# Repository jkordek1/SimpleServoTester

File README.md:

# SimpleServoTester

##
Still WIP

## About
Simple project for quick on-the-go servo testing. It has two different modes, manual one for controlling the servo position via rotary encoder and automatic (sweep) mode.
 
## Project status
- [x] Breadboard prototype
- [x] Schematic
- [x] PCB
- [ ] Enclosure design
- [ ] 3D CAD assembly and renders
- [ ] Assembly
- [ ] Programming

## Main features
- Based on popular ATmega328p microcontroller used on Arduino boards
- Powered by 2x18650 batteries
- IN219 current sense IC
- Rotary encoder for mode selection

## BOM
The components used are the ones that were available at-hand during the process of development. Therefore BOM for this project is not optimal.

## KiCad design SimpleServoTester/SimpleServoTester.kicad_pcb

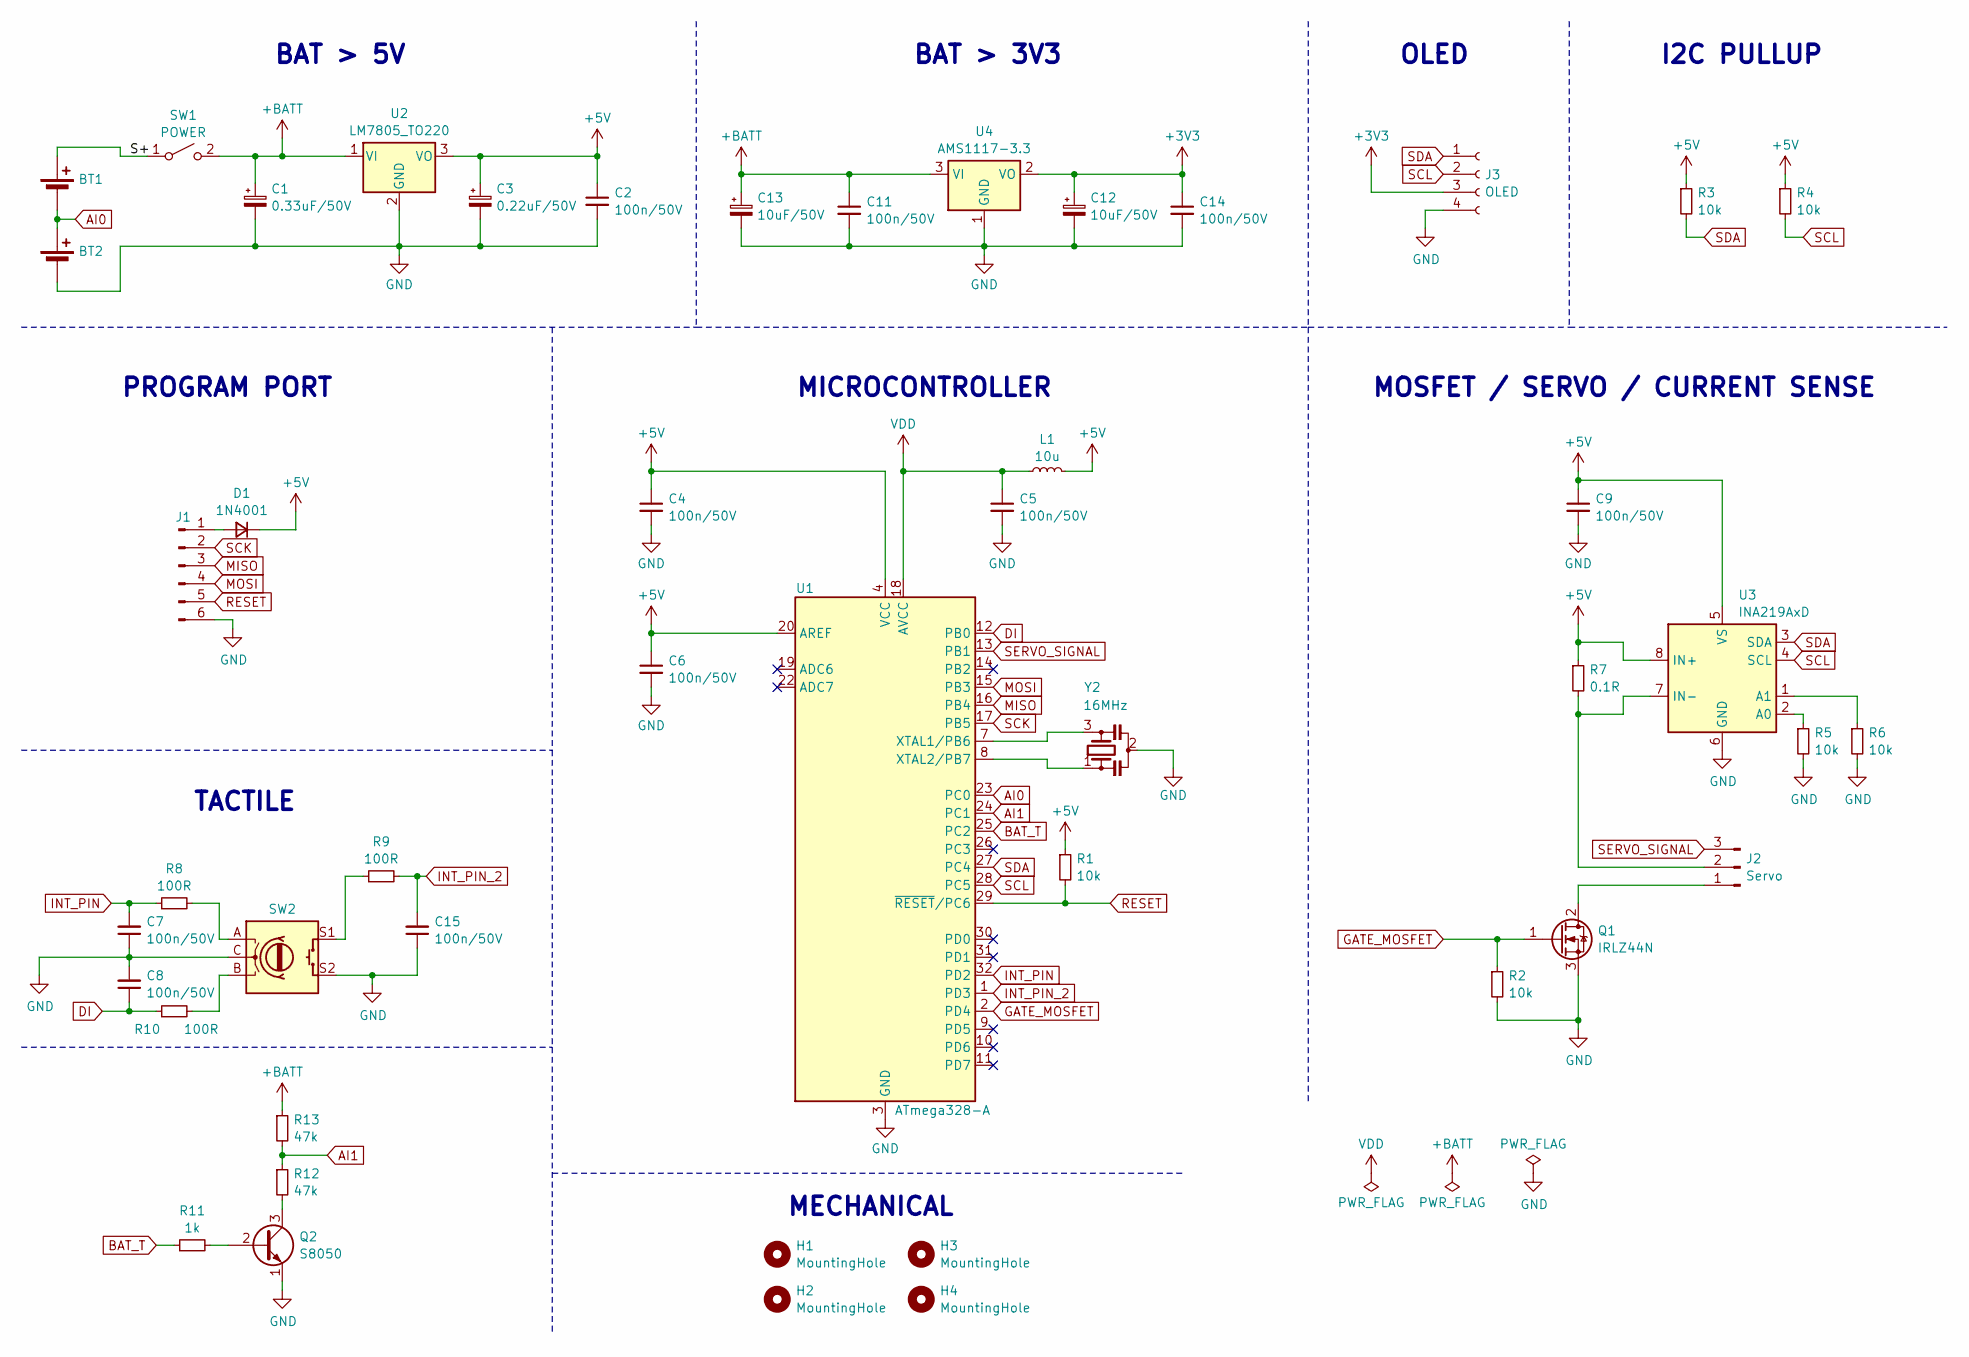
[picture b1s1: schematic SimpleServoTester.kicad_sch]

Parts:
BT1, BT2: Battery_Cell; 18650-PC2
C1: 0.33uF/50V; CP_Elec_5x5.4
C2, C4, C5, C6, C7, C8, C9, C11, C14, C15: 100n/50V; C_0603_1608Metric
C3: 0.22uF/50V; CP_Elec_5x5.4
C12, C13: 10uF/50V; CP_Elec_5x5.4
D1: 1N4001; D_SMA
H1, H2, H3, H4: MountingHole; MountingHole_3.2mm_M3
J1: USBASP; PinHeader_1x06_P2.54mm_Horizontal
J2: Servo; PinHeader_1x03_P2.54mm_Horizontal
J3: OLED; PinHeader_1x04_P2.54mm_Vertical
L1: 10u; L_1206_3216Metric
Q1: IRLZ44N; TO-220-3_Horizontal_TabDown
Q2: S8050; SOT-23-3
R1, R2, R3, R4, R5, R6: 10k; R_0603_1608Metric
R7: 0.1R; R_2512_6332Metric
R8, R9, R10: 100R; R_0603_1608Metric
R11: 1k; R_0603_1608Metric
R12, R13: 47k; R_0603_1608Metric
SW1: POWER; PinHeader_1x02_P2.54mm_Vertical
SW2: RotaryEncoder_Switch; RotaryEncoder_Alps_EC11E-Switch_Vertical_H20mm
U1: ATmega328-A; TQFP-32_7x7mm_P0.8mm
U2: LM7805_TO220; TO-220-3_Horizontal_TabDown
U3: INA219AxD; SOT-23-8
U4: AMS1117-3.3; SOT-223-3_TabPin2
Y2: 16MHz; CSTCE16M0V53-R0; JLCPCB Part # C32180

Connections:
+3V3: C12.1, C14.1, J3.3, U4.2 (VO)
+5V: C2.1, C3.1, C4.1, C6.1, C9.1, D1.1 (K), L1.2, R1.1, R3.1, R4.1, R7.1, U1.4 (VCC), U1.6 (VCC), U1.20 (AREF), U2.3 (VO), U3.5 (VS), U3.8 (IN+)
+BATT: C1.1, C11.1, C13.1, R13.1, SW1.2 (B), U2.1 (VI), U4.3 (VI)
/S+: BT1.1 (+), SW1.1 (A)
AI0: BT1.2 (-), BT2.1 (+), U1.23 (PC0)
AI1: R12.1, R13.2, U1.24 (PC1)
BAT_T: R11.1, U1.25 (PC2)
DI: C8.1, R10.1, U1.12 (PB0)
GATE_MOSFET: Q1.1 (G), R2.1, U1.2 (PD4)
GND: BT2.2 (-), C1.2, C2.2, C3.2, C4.2, C5.2, C6.2, C7.1, C8.2, C9.2, C11.2, C12.2, C13.2, C14.2, C15.1, J1.6, J3.4, Q1.3 (S), Q2.1 (E), R2.2, R5.2, R6.2, SW2.C, SW2.S2, U1.3 (GND), U1.5 (GND), U1.21 (GND), U2.2 (GND), U3.6 (GND), U4.1 (GND), Y2.2
INT_PIN: C7.2, R8.1, U1.32 (PD2)
INT_PIN_2: C15.2, R9.2, U1.1 (PD3)
MISO: J1.3, U1.16 (PB4)
MOSI: J1.4, U1.15 (PB3)
unnamed: D1.2 (A), J1.1
unnamed: J2.1, Q1.2 (D)
unnamed: J2.2, R7.2, U3.7 (IN-)
unnamed: Q2.2 (B), R11.2
unnamed: Q2.3 (C), R12.2
unnamed: R8.2, SW2.A
unnamed: R9.1, SW2.S1
unnamed: R10.2, SW2.B
unnamed: U1.7 (XTAL1/PB6), Y2.3
unnamed: U1.8 (XTAL2/PB7), Y2.1
unnamed: R5.1, U3.2 (A0)
unnamed: R6.1, U3.1 (A1)
RESET: J1.5, R1.2, U1.29 (~RESET/PC6)
SCK: J1.2, U1.17 (PB5)
SCL: J3.2, R4.2, U1.28 (PC5), U3.4 (SCL)
SDA: J3.1, R3.2, U1.27 (PC4), U3.3 (SDA)
SERVO_SIGNAL: J2.3, U1.13 (PB1)
VDD: C5.1, L1.1, U1.18 (AVCC)

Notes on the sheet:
OLED
TACTILE
BAT > 5V
I2C PULLUP
BAT > 3V3
MECHANICAL
MICROCONTROLLER
MOSFET / SERVO / CURRENT SENSE
PROGRAM PORT

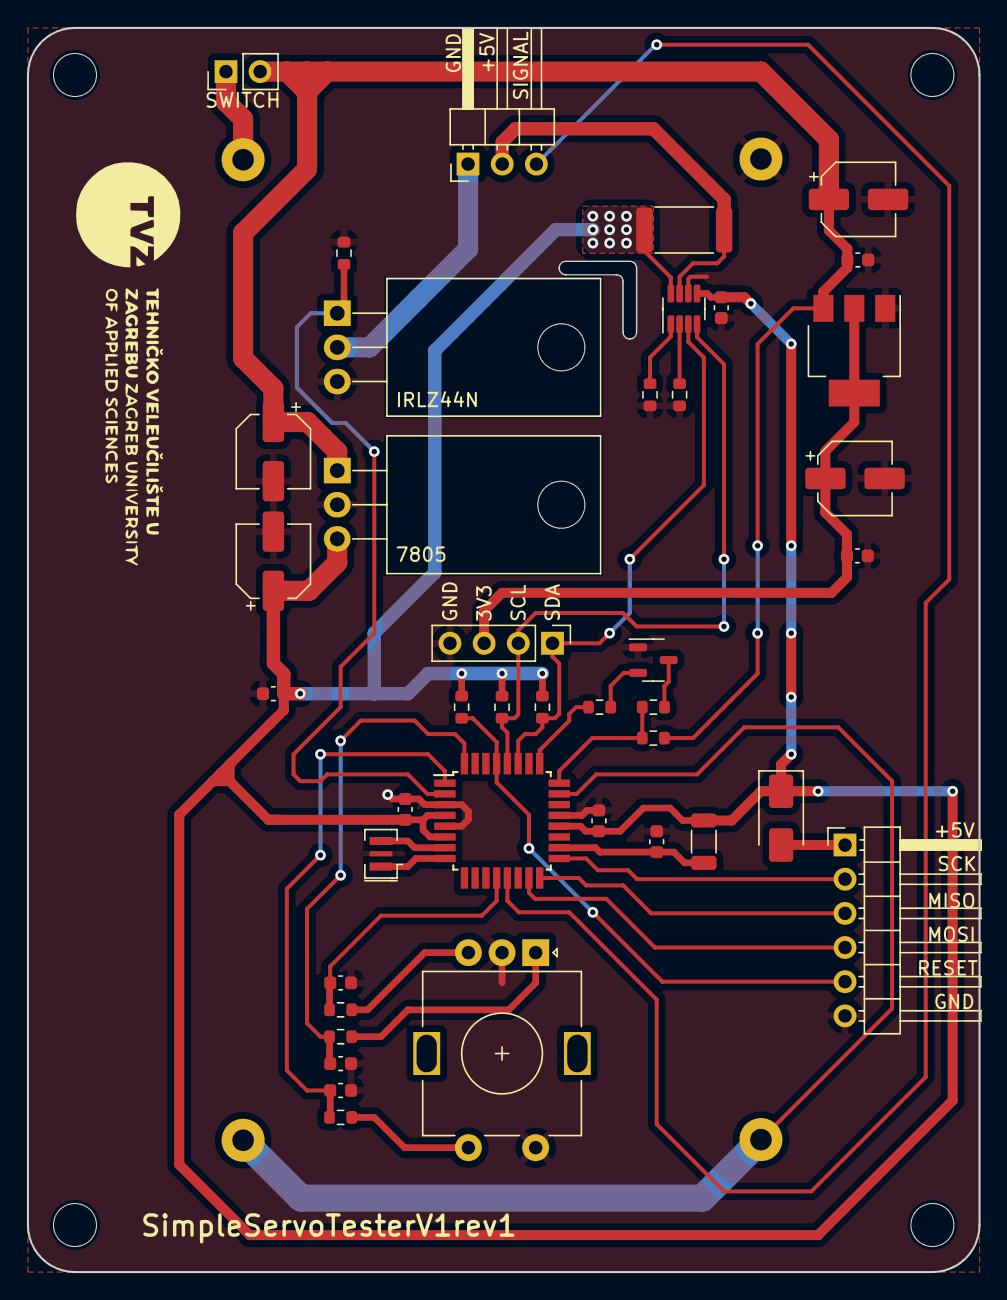
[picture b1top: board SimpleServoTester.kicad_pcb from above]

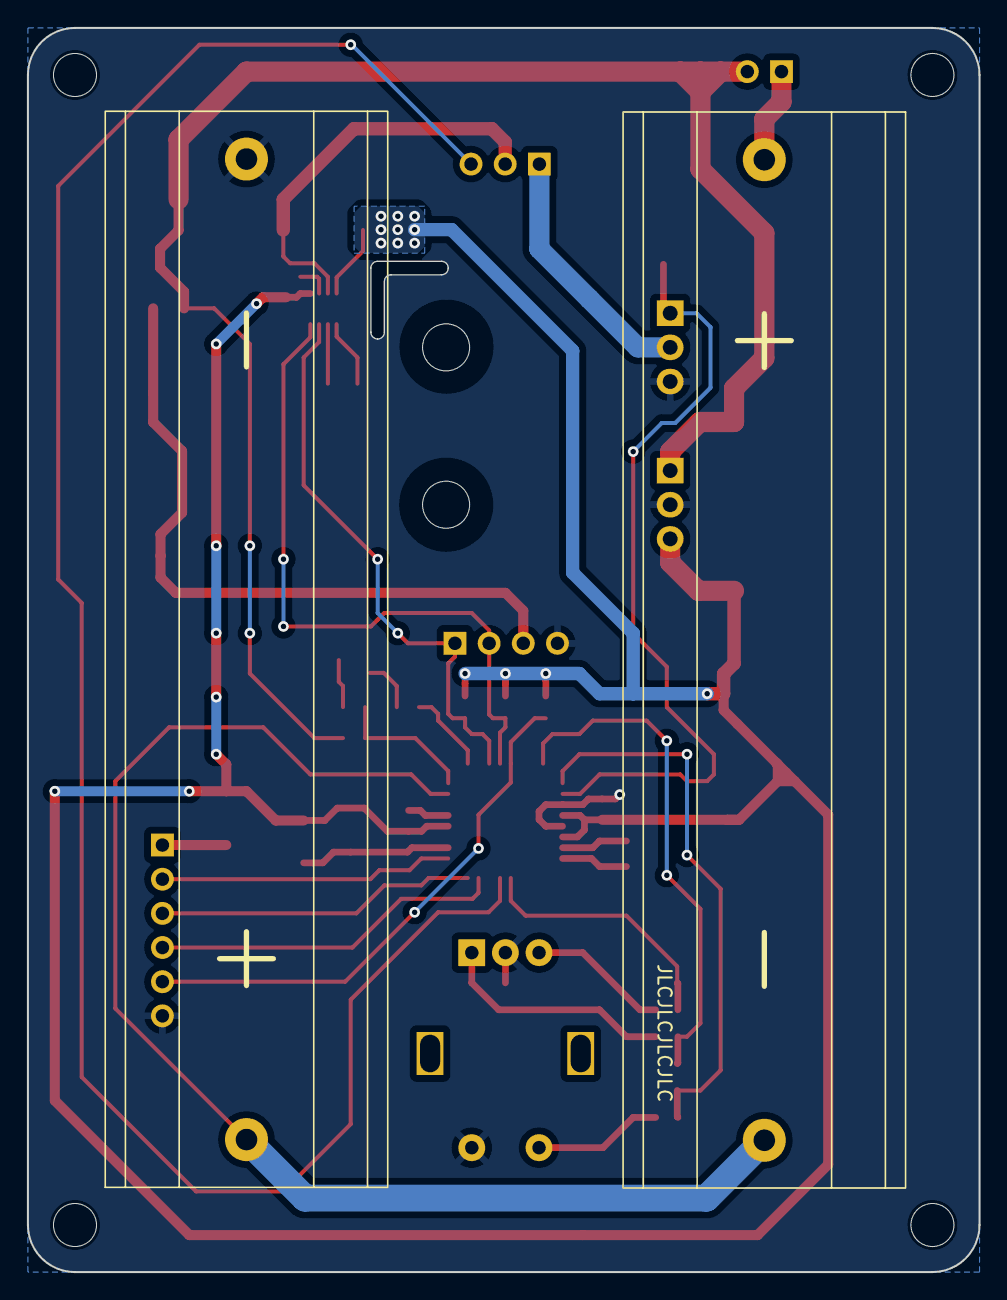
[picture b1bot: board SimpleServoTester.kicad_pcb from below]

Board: 2 copper layers, 70.8 x 92.5 mm, 47 parts (2 on the bottom side), 32 nets.

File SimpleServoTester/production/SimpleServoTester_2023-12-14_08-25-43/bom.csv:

Designator,Footprint,Quantity,Value,LCSC Part #
"BT1, BT2",18650-PC2,2,Battery_Cell,
C1,CP_Elec_5x5.4,1,0.33uF/50V,
"C11, C14, C15, C2, C4, C5, C6, C7, C8, C9",0603,10,100n/50V,
"C12, C13",CP_Elec_5x5.4,2,10uF/50V,
C3,CP_Elec_5x5.4,1,0.22uF/50V,
D1,D_SMA,1,1N4001,
"H1, H2, H3, H4",MountingHole_3.2mm_M3,4,MountingHole,
J1,PinHeader_1x06_P2.54mm_Horizontal,1,USBASP,
J2,PinHeader_1x03_P2.54mm_Horizontal,1,Servo,
J3,PinHeader_1x04_P2.54mm_Vertical,1,OLED,
L1,1206,1,10u,
Q1,TO-220-3_Horizontal_TabDown,1,IRLZ44N,
Q2,SOT-23-3,1,S8050,
"R1, R2, R3, R4, R5, R6",0603,6,10k,
"R10, R8, R9",0603,3,100R,
R11,0603,1,1k,
"R12, R13",0603,2,47k,
R7,2512,1,0.1R,
SW1,PinHeader_1x02_P2.54mm_Vertical,1,POWER,
SW2,RotaryEncoder_Alps_EC11E-Switch_Vertical_H20mm,1,RotaryEncoder_Switch,
U1,TQFP-32_7x7mm_P0.8mm,1,ATmega328-A,
U2,TO-220-3_Horizontal_TabDown,1,LM7805_TO220,
U3,SOT-23-8,1,INA219AxD,
U4,SOT-223-3_TabPin2,1,AMS1117-3.3,
Y2,CSTCE16M0V53-R0,1,16MHz,C32180

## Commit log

2023-12-14 Initial release
